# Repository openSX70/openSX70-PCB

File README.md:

# openSX70-PCB
EagleCAD design files for the main PCB of the openSX70 project

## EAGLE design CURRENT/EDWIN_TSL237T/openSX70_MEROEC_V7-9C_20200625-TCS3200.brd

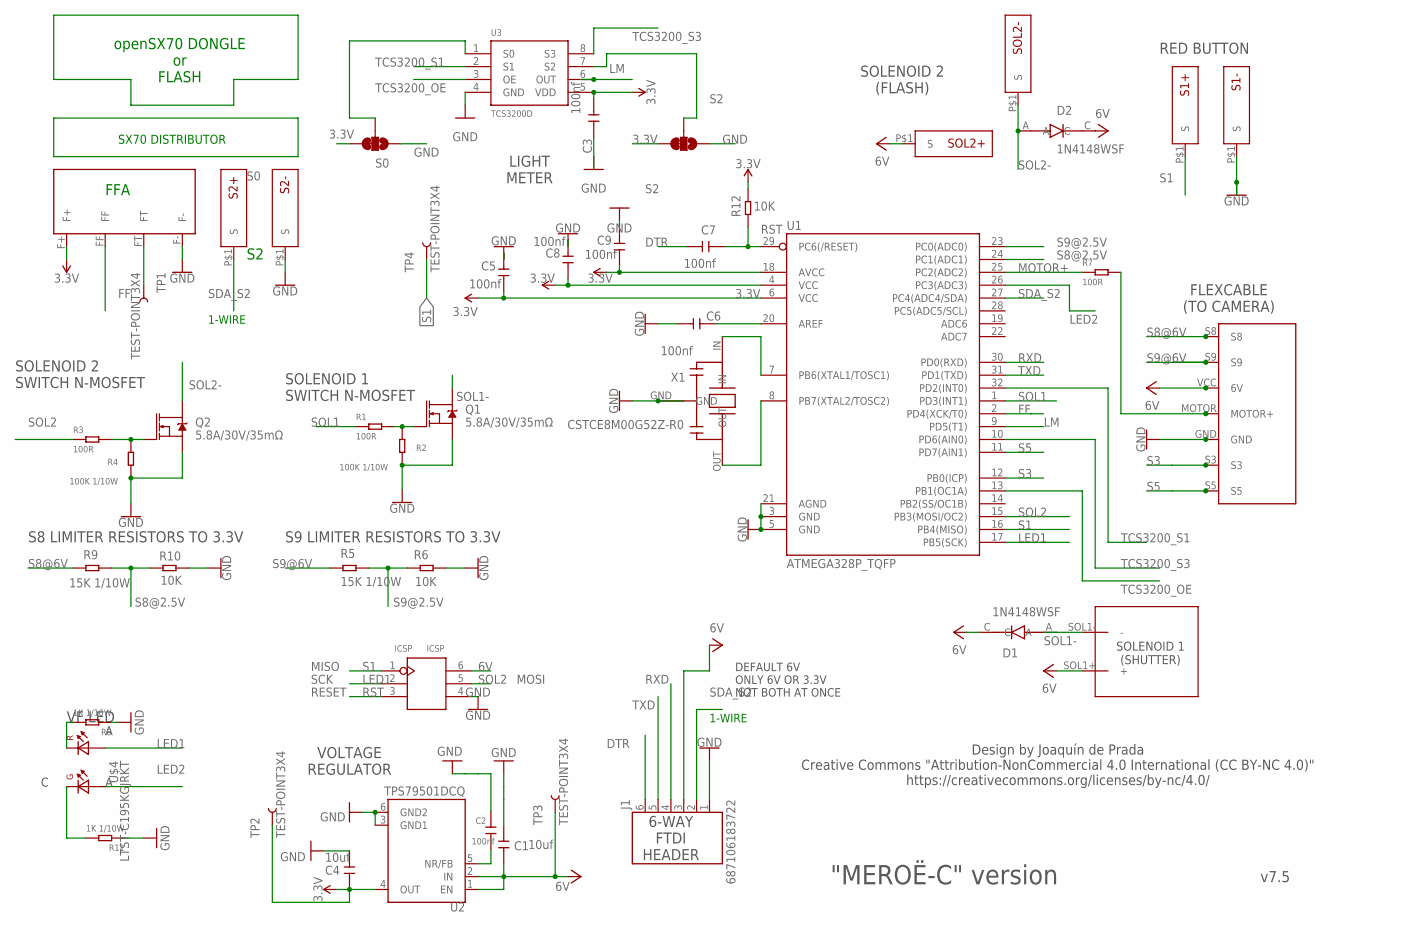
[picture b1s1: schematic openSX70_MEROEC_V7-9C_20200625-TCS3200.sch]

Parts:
C1, C4: 10uf; C0603
C2, C3, C5, C6, C7, C8, C9: 100nf; C0603
D1, D2: 1N4148WSF; SODFL2512X100N
ICSP: ICSP; H2X3-2.54
J1: 687106183722
Q1, Q2: 5.8A/30V/35mΩ; SOT23-3
R1, R3, R7: 100R; R0603
R2, R4: 100K 1/10W; R0603
R5, R9: 15K 1/10W; R0603
R6, R10, R12: 10K; R0603
R8, R11: 1K 1/10W; R0603
S0: S0; SMT-JUMPER_3_1-NC_TRACE_SILK
S1+, S1-, S2+, S2-: SX70-S-PAD-NEW; SX70-S-PAD2
S2: S2; SMT-JUMPER_3_1-NC_TRACE_SILK
SOL1: SX70-SOLENOID1-2PADS; SX70-SOLENOID1-2
SOL2+, SOL2-: SX70-S-PAD-NEW; SX70-S-PAD2
TP1, TP2, TP3, TP4: TEST-POINT3X4; PAD.03X.04
U1: ATMEGA328P_TQFP; TQFP32-08
U2: TPS79501DCQ; SOT127P706X180-6N
U3: TCS3200D; SOIC8
U$1: SX70-7-PAD; SX70-7-PAD-PROPER
U$2: FFA; FFA-PAD-PACKAGE
U$4: LTST-C195KGJRKT; LTST-BILED-15X16
X1: CSTCE8M00G52Z-R0; CFP95P160X100-3N

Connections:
3.3V: C3.1, C4.2, C5.1, C8.1, C9.1, R12.2, S0.3, S2.3, TP2.P$1, U1.4 (VCC), U1.6 (VCC), U1.18 (AVCC), U2.4 (OUT), U3.5 (VDD), U$2.F+
6V: C1.2, D1.C, D2.C, ICSP.6 (VCC), J1.3 (4), SOL1.SOL1+ (+), SOL2+.P$1, TP3.P$1, U2.1 (EN), U2.2 (IN), U$1.VCC (6V)
DTR: C7.1, J1.6 (1)
FF: U1.2 (PD4(XCK/T0)), U$2.FF
GND: C1.1, C2.1, C3.2, C4.1, C5.2, C6.1, C8.2, C9.2, ICSP.4 (GND), J1.1 (6), Q1.2 (S), Q2.2 (S), R2.1, R4.1, R6.2, R8.1, R10.2, R11.1, S0.1, S1-.P$1, S2.1, S2-.P$1, U1.3 (GND), U1.5 (GND), U1.21 (AGND), U2.3 (GND1), U2.6 (GND2), U3.4 (GND), U$1.GND, U$2.F-, X1.GND
LED1: ICSP.2 (SCK), U1.17 (PB5(SCK)), U$4.P$2 (A2)
LED2: U1.26 (PC3(ADC3)), U$4.P$1 (A1)
LM: U1.9 (PD5(T1)), U3.6 (OUT)
MOTOR+: R7.1, U1.25 (PC2(ADC2))
MOTOR-HEADER: R7.2, U$1.MOTOR (MOTOR+)
unnamed: Q1.1 (G), R1.2, R2.2
unnamed: C6.2, U1.20 (AREF)
unnamed: Q2.1 (G), R3.2, R4.2
unnamed: U1.7 (PB6(XTAL1/TOSC1)), X1.IN
unnamed: TP1.P$1, U$2.FT
unnamed: U1.8 (PB7(XTAL2/TOSC2)), X1.OUT
unnamed: S0.2, U3.1 (S0)
unnamed: S2.2, U3.7 (S2)
unnamed: R8.2, U$4.P$4 (K2)
unnamed: C2.2, U2.5 (NR/FB)
unnamed: R11.2, U$4.P$3 (K1)
RST: C7.2, ICSP.3 (RST), R12.1, U1.29 (PC6(/RESET))
RXD: J1.4 (3), U1.30 (PD0(RXD))
S1: ICSP.1 (MISO), S1+.P$1, TP4.P$1, U1.16 (PB4(MISO))
S3: U1.12 (PB0(ICP)), U$1.S3
S5: U1.11 (PD7(AIN1)), U$1.S5
S8@2.5V: R9.2, R10.1, U1.24 (PC1(ADC1))
S8@6V: R9.1, U$1.S8
S9@2.5V: R5.2, R6.1, U1.23 (PC0(ADC0))
S9@6V: R5.1, U$1.S9
SDA_S2: J1.2 (5), S2+.P$1, U1.27 (PC4(ADC4/SDA))
SOL1: R1.1, U1.1 (PD3(INT1))
SOL1-: D1.A, Q1.3 (D), SOL1.SOL1- (-)
SOL2: ICSP.5 (MOSI), R3.1, U1.15 (PB3(MOSI/OC2))
SOL2-: D2.A, Q2.3 (D), SOL2-.P$1
TCS3200_OE: U1.13 (PB1(OC1A)), U3.3 (OE)
TCS3200_S1: U1.32 (PD2(INT0)), U3.2 (S1)
TCS3200_S3: U1.10 (PD6(AIN0)), U3.8 (S3)
TXD: J1.5 (2), U1.31 (PD1(TXD))

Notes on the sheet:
1-WIRE
FFA
LIGHT METER
FLEXCABLE (TO CAMERA)
RED BUTTON
SOLENOID 1 (SHUTTER)
SOLENOID 2 (FLASH)
6-WAY FTDI HEADER
VOLTAGE REGULATOR
S8 LIMITER RESISTORS TO 3.3V
S9 LIMITER RESISTORS TO 3.3V
SOLENOID 2 SWITCH N-MOSFET
SOLENOID 1 SWITCH N-MOSFET
SX70 DISTRIBUTOR
openSX70 DONGLE or FLASH
v7.5
Design by Joaquín de Prada Creative Commons "Attribution-NonCommercial 4.0 International (CC BY-NC 4.0)" https://creativecommons.org/licenses/by-nc/4.0/
"MEROË-C" version
DEFAULT 6V ONLY 6V OR 3.3V NOT BOTH AT ONCE
MISO
SCK
RESET
MOSI
VF LED

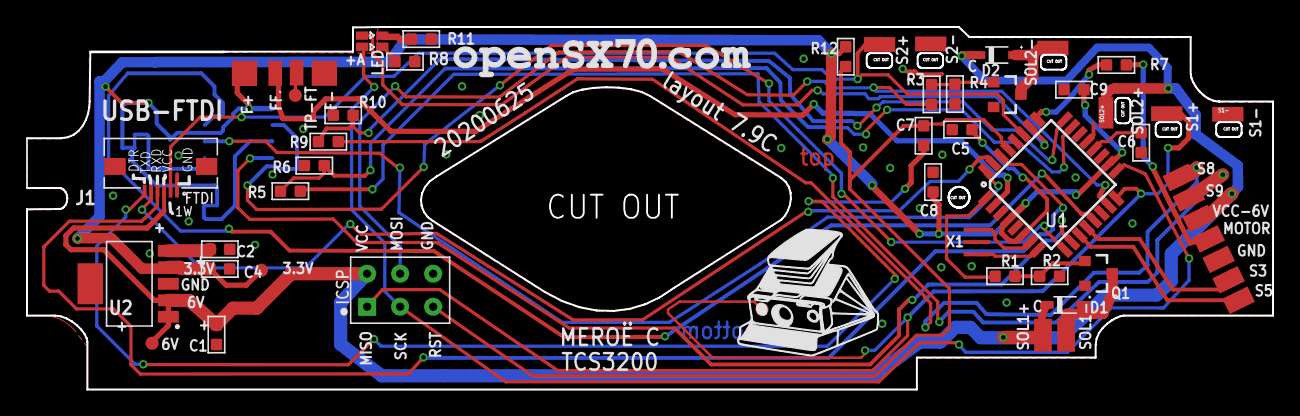
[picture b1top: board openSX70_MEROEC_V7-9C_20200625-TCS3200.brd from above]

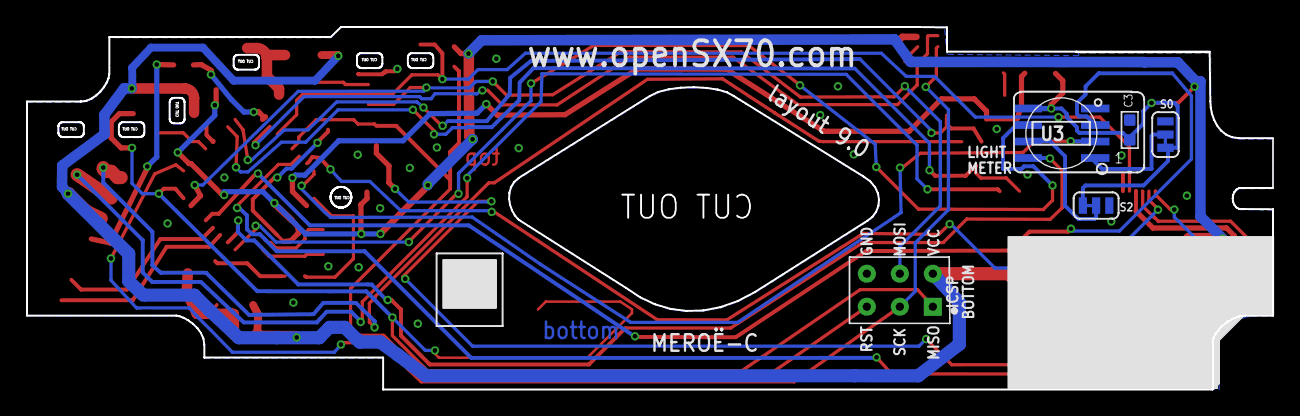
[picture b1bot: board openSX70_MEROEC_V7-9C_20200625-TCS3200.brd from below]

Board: 2 copper layers, 95.9 x 27.9 mm, 47 parts (4 on the bottom side), 39 nets.

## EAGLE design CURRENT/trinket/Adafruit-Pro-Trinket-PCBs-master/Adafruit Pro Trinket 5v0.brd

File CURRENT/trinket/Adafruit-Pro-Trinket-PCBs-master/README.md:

Adafruit-Pro-Trinket-PCBs
=========================

PCB files for Adafruit Pro Trinket 3V & 5V

This is the CAD & PCB data for the Adafruit Trinket
PCB format is EagleCAD schematic and board layout

For more details, check out the product pages at

-----> https://www.adafruit.com/products/2000
and
-----> https://www.adafruit.com/products/2010

Adafruit invests time and resources providing this open source design, 
please support Adafruit and open-source hardware by purchasing 
products from Adafruit!

Designed by Adafruit Industries.  
Creative Commons Attribution, Share-Alike license, check license.txt for more information
All text above must be included in any redistribution

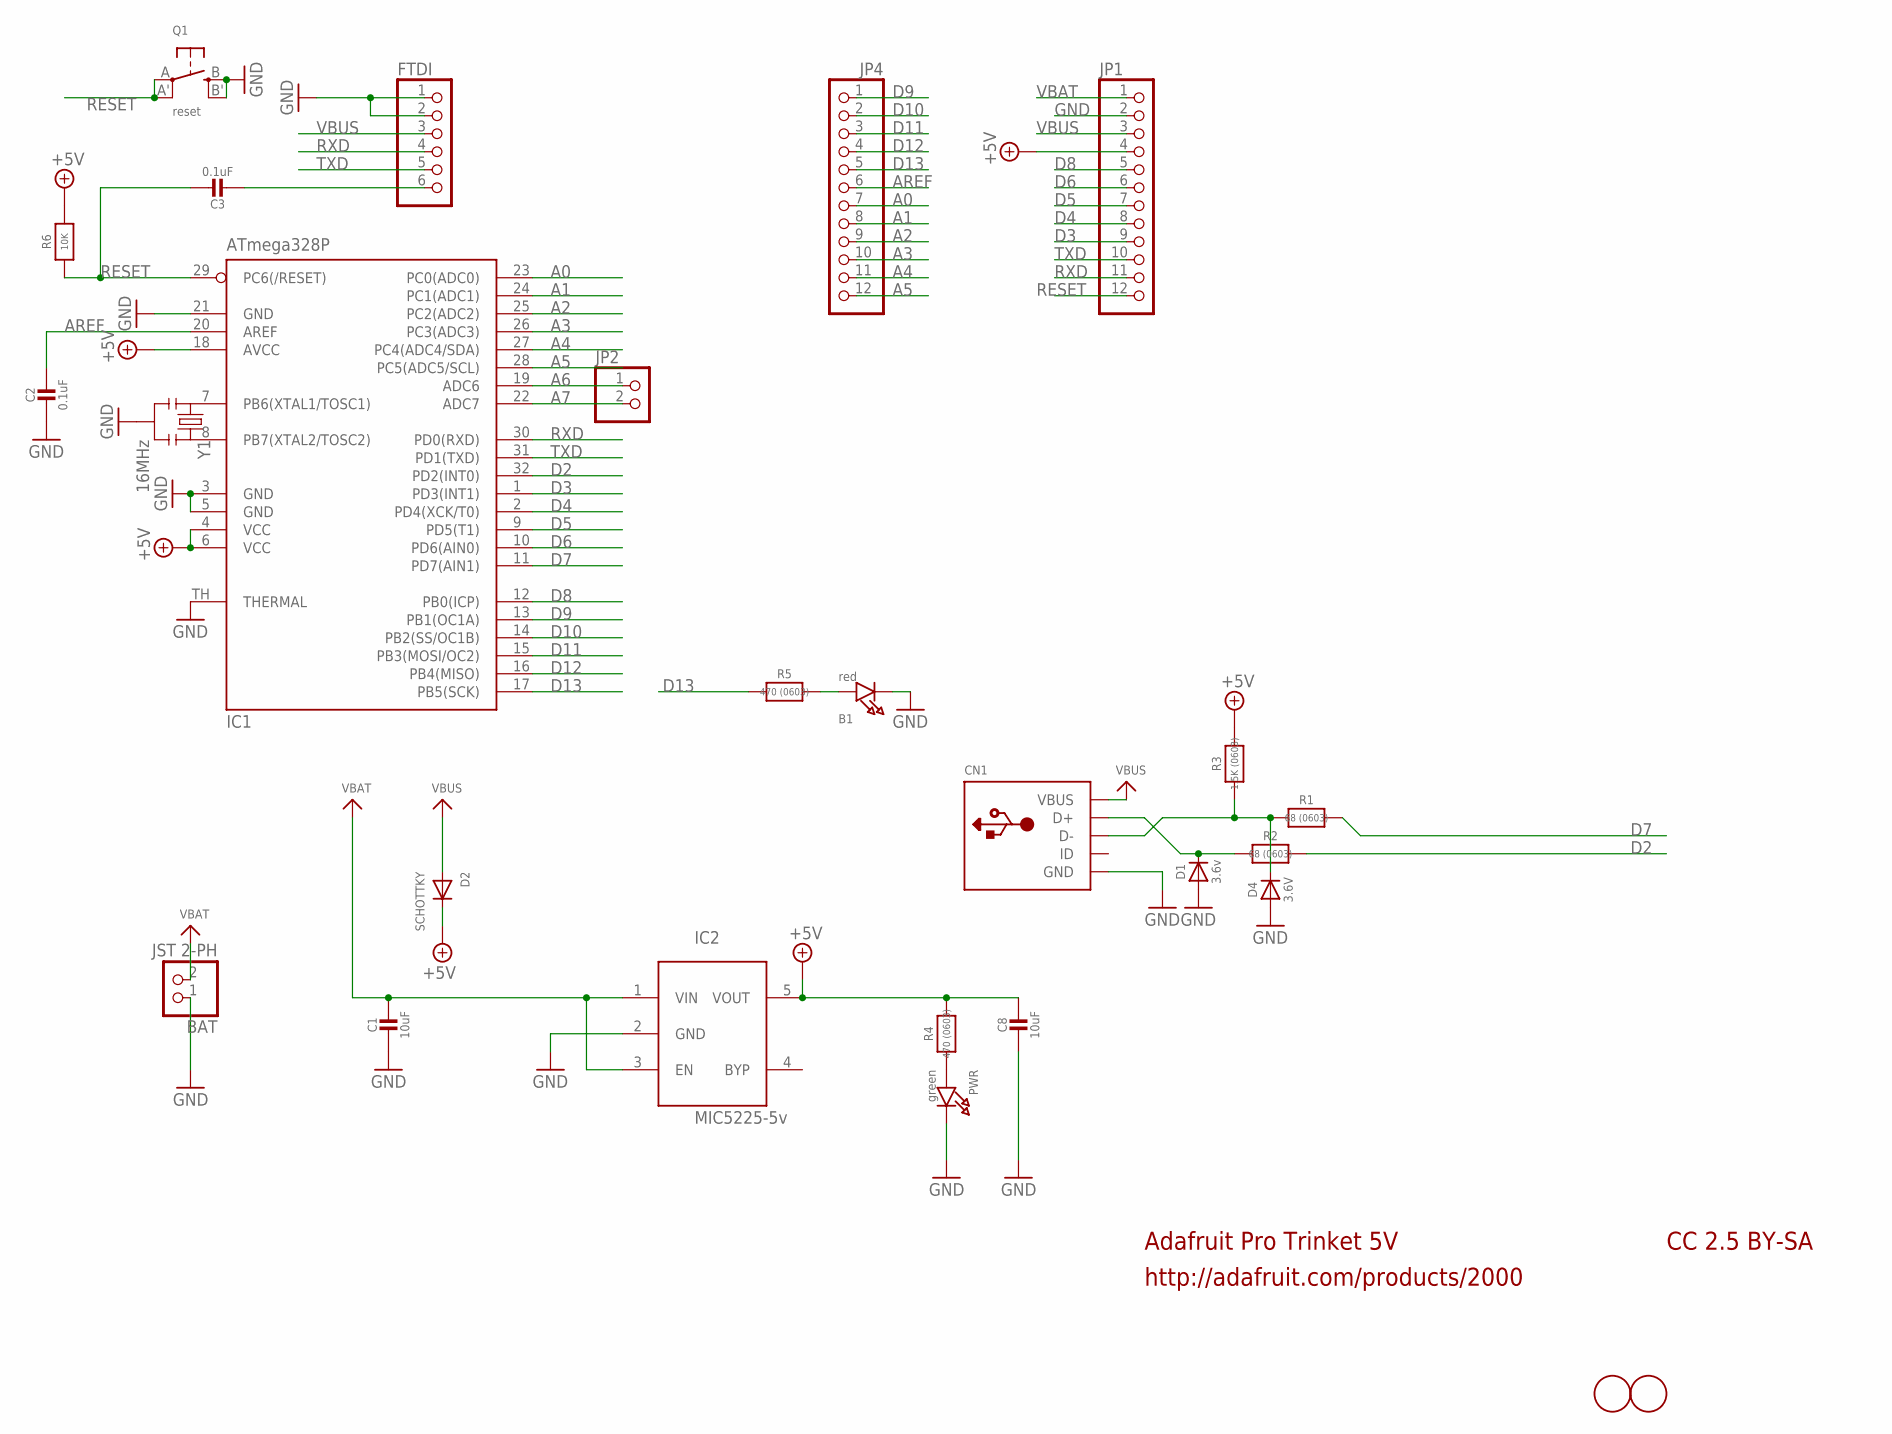
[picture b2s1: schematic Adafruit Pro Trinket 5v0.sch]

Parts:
B1: red; CHIPLED_0805_NOOUTLINE
BAT: JST 2-PH; JSTPH2
C1, C8: 10uF; 0805-NO
C2: 0.1uF; _0805MP
C3: 0.1uF; 0805-NO
CN1: USBMICRO_20329; 4UCONN_20329
D1: 3.6v; SOD-323
D2: SCHOTTKY; SOD-123FL
D4: 3.6V; SOD-323
FTDI: PINHD-1X6CB; 1X06-CLEANBIG
IC1: ATmega328P; MLF32-TH
IC2: MIC5225-5v; SOT23-5L
JP1, JP4: PINHD-1X12-CB; 1X12-CB
JP2: HEADER-1X2ROUND; 1X02_ROUND
PWR: green; CHIPLED_0805_NOOUTLINE
Q1: reset; BTN_KMR2_4.6X2.8
R1, R2: 68 (0603); 0603-NO
R3: 1.5K (0603); 0603-NO
R4, R5: 470 (0603); 0603-NO
R6: 10K; 0805-NO
U$1, U$6: FIDUCIAL; FIDUCIAL_1MM
Y1: 16MHz; RESONATOR-SMD

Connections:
+5V: C8.1, D2.C, IC1.4 (VCC), IC1.6 (VCC), IC1.18 (AVCC), IC2.5 (VOUT), JP1.4, R3.2, R4.2, R6.2
A0: IC1.23 (PC0(ADC0)), JP4.7
A1: IC1.24 (PC1(ADC1)), JP4.8
A2: IC1.25 (PC2(ADC2)), JP4.9
A3: IC1.26 (PC3(ADC3)), JP4.10
A4: IC1.27 (PC4(ADC4/SDA)), JP4.11
A5: IC1.28 (PC5(ADC5/SCL)), JP4.12
A6: IC1.19 (ADC6), JP2.1
A7: IC1.22 (ADC7), JP2.2
AREF: C2.1, IC1.20 (AREF), JP4.6
D2: IC1.32 (PD2(INT0)), R2.2
D3: IC1.1 (PD3(INT1)), JP1.9
D4: IC1.2 (PD4(XCK/T0)), JP1.8
D5: IC1.9 (PD5(T1)), JP1.7
D6: IC1.10 (PD6(AIN0)), JP1.6
D7: IC1.11 (PD7(AIN1)), R1.2
D8: IC1.12 (PB0(ICP)), JP1.5
D9: IC1.13 (PB1(OC1A)), JP4.1
D10: IC1.14 (PB2(SS/OC1B)), JP4.2
D11: IC1.15 (PB3(MOSI/OC2)), JP4.3
D12: IC1.16 (PB4(MISO)), JP4.4
D13: IC1.17 (PB5(SCK)), JP4.5, R5.2
D+: CN1.D+, D1.C, R2.1
D-: CN1.D-, D4.C, R1.1, R3.1
DTR/RTS: C3.2, FTDI.6
GND: B1.C, BAT.1, C1.2, C2.2, C8.2, CN1.BASE@1 (GND), CN1.BASE@2 (GND), CN1.GND, CN1.SPRT@1 (GND), CN1.SPRT@2 (GND), CN1.SPRT@3 (GND), CN1.SPRT@4 (GND), D1.A, D4.A, FTDI.1, FTDI.2, IC1.3 (GND), IC1.5 (GND), IC1.21 (GND), IC1.TH (THERMAL), IC2.2 (GND), JP1.2, PWR.C, Q1.B (S), Q1.B' (S1), Y1.2
unnamed: B1.A, R5.1
unnamed: IC1.8 (PB7(XTAL2/TOSC2)), Y1.3
unnamed: IC1.7 (PB6(XTAL1/TOSC1)), Y1.1
unnamed: PWR.A, R4.1
RESET: C3.1, IC1.29 (PC6(/RESET)), JP1.12, Q1.A, Q1.A' (P1), R6.1
RXD: FTDI.4, IC1.30 (PD0(RXD)), JP1.11
TXD: FTDI.5, IC1.31 (PD1(TXD)), JP1.10
VBAT: BAT.2, C1.1, IC2.1 (VIN), IC2.3 (EN), JP1.1
VBUS: CN1.VBUS, D2.A, FTDI.3, JP1.3

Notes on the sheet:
Adafruit Pro Trinket 5V
http://adafruit.com/products/2000
CC 2.5 BY-SA

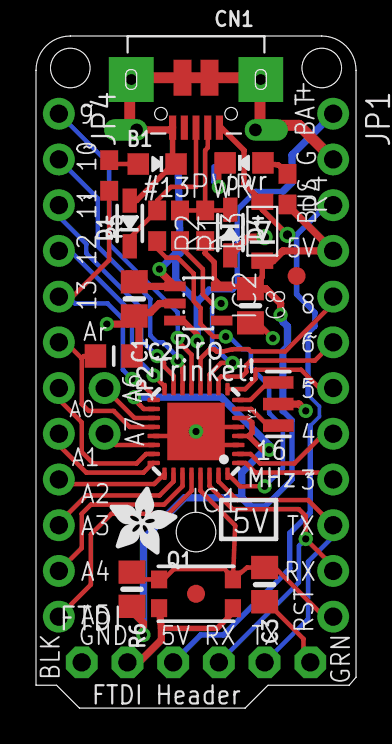
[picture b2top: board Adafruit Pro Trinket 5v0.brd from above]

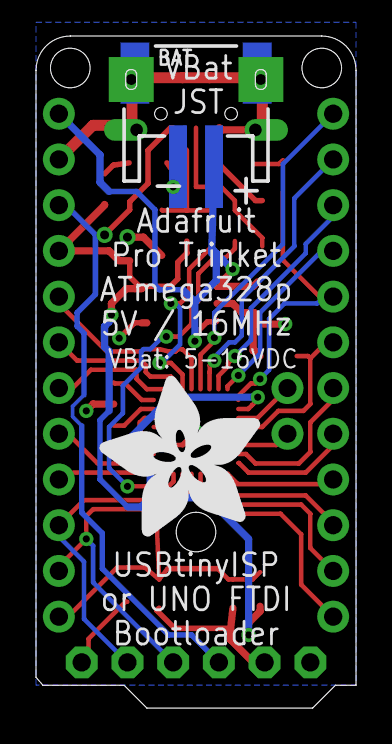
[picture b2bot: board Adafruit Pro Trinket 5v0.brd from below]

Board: 2 copper layers, 17.8 x 37.3 mm, 29 parts (2 on the bottom side), 35 nets.

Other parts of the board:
U$7: ADAFRUIT_3.5MM
U$9: ADAFRUIT_9MM

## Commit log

2017-11-27 set the CC BY-NC 4.0 license for hardware stuff
    You are free to:
    Share — copy and redistribute the material in any medium or format
    Adapt — remix, transform, and build upon the material
    The licensor cannot revoke these freedoms as long as you follow the license terms.
2017-11-27 initial commit of files
    These are the board and the schematic, initial design
2017-11-27 the DXF outline files
    Files you import to create the Dimension layer on Eagle.
2017-11-27 more DXF outline files
    Updated DXF files. Not checked yet
2017-11-27 Eagle schematic and board with connectors
    Eagle schematic and board with connectors. The components are not placed. Good start point to design your own board from scratch.
2017-11-27 Eagle openSX70 pcb layout 2.0
    Layout 2.0
2017-11-27 Eagle main PCB 2.1
    Eagle main PCB 2.1, manufactured by EasyEDA as a test 26/11/2017
2017-11-27 openSX70 main PCB gerbers
    for SEEDSTUDIO FUSION and EasyEDA, check at least .8mm, probably better .6mm or .4mm witdh of the board!
2017-12-16 New "RAW" as a startup for new placement/layout. Changed crystal for one smaller and with caps built in. Created files for new WIP.
2017-12-18 new board work in progress.
2017-12-18 small steps on the board.
2017-12-20 Changed MOTOR pin from 19 to 25. The board is a mess and I have to start over.
2017-12-20 change MOTOR to pin 25 on RAW file.
2017-12-20 new RAW version and WIP version with MOTOR+ to pin 25. RAW version without component layout on board to start from scratch.
2017-12-20 New up-to-date WIP file!
2017-12-21 minor updates in new layout. Routing manually important traces.
2017-12-24 Painfully laying out components and routing, manually.
2017-12-25 Saved a pre-AR version and then different WIP AR.
2017-12-25 Added some vias.
2017-12-29 fixed connections on openSX70 library
2018-01-02 V3.2 added license text. Will do to all brd.
2018-01-02 New version 3.3 changed diode to DZ2J033
2018-01-03 Create new 3.4 "chocolate" version. Looks ok, will do more tests and send it for fabrication. Also created gerbers, remember minimun .8mm, better .6mm or .4mm.
2018-01-03 minor cosmetic changes to "chocolate"
2018-01-03 More cosmetic stuff.
2018-01-03 Added on copper top and bottom for sanity
2018-01-03 I messed versions work/home
2018-01-03 Version 3.4.1 "Chocolate" changed D1 to 1N4148W SOD-123 diode. Created gerbers
2018-01-03 fixed some stuff in the schematic
2018-01-03 Added BOM excel file
2018-01-03 Added correct version number in bottom
2018-01-16 New version 3.5, fixed D1 footprint and some tracks. Added an FTDI 3.3v-6V selection jumper. Change version name to cake
2018-01-16 Lots of small fixes, and fixed cosmetically values, widening track and such.
2018-01-17 New version to fix Solenoid#1 pin error. Minor fix.
2018-01-17 Minor 45º fixes ;-)
2018-01-17 changed sol#1 and FF port to what it should be.
2018-01-17 changed version number and name on schematic
2018-01-17 Changed name on brd and version number.
2018-01-17 Added a protection diode D1 to solenoid#1 for protection. I had assumed that it was built in the solenoid but Phyvine Tong indicated that some later models (alpha) don't have it.
2018-01-17 Added GND 6V and 3.3V test points. Removed a bunch of innecessary vias.
2018-01-17 I keep on tweaking compulsively. Definitely have to stop.
2018-01-18 Added TP to pins 15 16 and 17, for bootloader programming (?)
2018-01-18 Minor fixes, making the board look nicer.
2018-01-18 Minor changes, also added TP SCL and SDA. Created gerbers.
2018-01-18 Cosmetic changes and moved some files (chocolate) to OLD folder.
2018-01-19 Made main 6v track wider from 32mil to 40mil.
2018-01-19 Widening more tracks.
2018-01-19 Latest update
2018-01-19 Outline of the light seal Just lost a bunch of work!!
2018-01-20 Upped to v. 3.7 and changed the date.
2018-01-20 Trying a new component layout, saving the lens seal! NOT ROUTED use Aladdin for now
2018-01-22 Lost track of what I was doing, but basically trying to stay out of the light seal.
2018-01-22 "Saved" Aladdin regarding light-seal issue. Will manufacture. Current 2.8
2018-01-22 final Aladdin v.3.9
2018-01-22 Armonized all VIAS. Minor aesthetic fixes.
2018-01-22 New board design with a FCC or FPC.
2018-01-23 New v.3.9 "Aladdin-fpc" is basically Aladdin with the FTDI header changed to the upper left in the form of a flexible cable.
2018-01-23 Minor changes to Aladdin-fpc 3.9
2018-01-23 Minor changed to v.3.9 FPC with a flat cable .5mm for the FTDI. It is a variant based on the Aladdin v3.8
2018-01-23 Fixing little things in all Aladdin boards
2018-01-24 Minor retouches
2018-01-24 Changes from the office
2018-01-24 Latest and greatest. Go to production????
2018-01-24 Changed MISO/MOSI was all wrong
2018-01-24 This is the newest today.
2018-01-24 trying to figure out Github. From home.
2018-01-25 Changes silkscreen to 2.5V new version 2.9.1
2018-01-26 Manufactured board
2018-02-05 New Aladdin-FPC "C" version
2018-02-06 working on a "manufacturable" board
2018-02-07 Very minor change, making room for programming pad
2018-02-07 Working on an ICSP header
2018-02-08 NEW VERSION 3.9.5S for SeeedStudio Fusion PCBA test
2018-02-09 Removed unnecessary vias, al pads. Minor fixes all over. Getting ready for production!
2018-02-09 new BOM "mix"
2018-02-10 working on a manufacturable version
2018-02-10 Lots of changes in SEEED studio NOW 3.9.6S. Moved a lot of files to OLD folders.
2018-02-11 Working
2018-02-13 New "anniversary" SEEED-only (WIP) PCBA version
2018-02-13 New BOM and new PCB all OPL CPL parts for manufacturing!
2018-02-13 Cleaned the schematic a bit
2018-02-19 changes, octopart BOM
2018-02-19 changed to OPL and CPL footprints
2018-02-19 Seeed components
2018-02-20 Updated to 8.6.3 eagle and more
2018-02-20 Updated office to 8.6.3 minor changes. Rethinking buzzer altogether
2018-02-21 retouches from home. Thinking about a buzzer fix, working on a 10-way FPC both ISCP and FTDI at once
2018-02-21 assembly cues
2018-02-21 Latest with new Buzzer schematic
2018-02-21 Clean-up board and schematic
2018-02-21 Tweaking and tweaking to keep the mind busy.
2018-02-22 And so on...
2018-02-22 New board nickname: Len's&Bellows 5.0 (different from Len's & Bellows 4.x): moved Atmega up, and much more little improvements!
2018-02-23 Major folder rearrangement, latest 5.0 Lens-and-Bellows
2018-02-23 All ready for manufacture!
2018-02-26 New 5.1 version
2018-02-26 Latest versions bypassing Sourcetree
    SourceTree not working from home, tried everything to no avail.
2018-02-26 New "definitive" Len's and Bellows version.
2018-03-27 Current
2018-04-21 Merge branch 'master' of https://github.com/openSX70/openSX70-PCB
    # Conflicts:
    # CURRENT/openSX70_LENS&BELLOWS_V5.2-SEEED_20180226.dxf
2018-05-21 New 5.5 version need a new code-name
2018-05-23 New 5,5 "Pathfinder" with relocated BH1750 and removed buzzer.
2018-06-06 Pathfinder
2018-07-11 updates.
2018-10-05 new layout6 PCB WIP
2018-10-05 Clean up
2018-10-05 NEW NAME FOR LAYOUT 6.0 ALPHA
2018-10-08 working on "ALPHA"
2018-10-08 added quotes to "ALPHA" in the board
2018-10-09 new experimental 6.2: I find no way to fit the FPC connector oposite on the PCB of where it is now, there is just no space.
2018-10-10 ADDED S4A S4B and resistor through jumper J2
2018-10-11 added resistors for different sensor sensibilities
2018-10-15 New layout 6.5 with new flexcable custom connector
2018-10-16 adding to the board
2018-10-24 Work in progress
2018-10-27 acccidentally modified?
2018-10-31 new 7-pad (fixed the component) and WIP on the LED, new LED dual SMD
2018-11-01 new all new layout 7.0
2018-11-02 backtracking to a more safe 6.2.2 version
2018-11-02 working on 6.2.2
2018-11-02 v7 probably abandoned
2018-11-02 6.2.1 WIP
2018-11-03 new board ready for manufacturing 6.2.2
2018-11-04 new layout minor changes
2018-11-04 changed connector S-pad on 6.2.3
2018-11-04 minor fixes or picture graphic
2018-11-04 yet again, new gerbers too
2018-11-05 Simblee eagle files from Sparkfun
2018-11-05 WORKING WITH THE SMALLER ATMEL
2018-11-22 ALPHA BOM (not final)
2018-11-27 new LED outline
2018-11-29 new LED footprint!
2018-12-19 New 6.2.5
2018-12-21 new main PCB fixed 3rd resistor on Photodiode!
2019-02-12 gerbers
2019-03-09 working on new Layout with voltage to frequency AD654 "U2"
2019-03-09 few changes
2019-06-03 organized folders and new PCB for TCS3200 Meröe
2019-06-03 Meröe more or less finished. TCS3200
2019-06-04 NEW RAISED LEDs
2019-06-04 finished Meröe working on TSL235R
2019-06-05 adding decoupling caps
2019-06-05 TSL235 test
2019-06-06 New Meroë 7.5 with 3 added capacitors. Crowded
2019-06-06 completely new layout
2019-06-07 more or less finalised for all 3 chips
2019-11-14 Major cleanup, latest working
2020-04-07 new files and reorganization
2021-01-29 Latest PCBs that I feel confident to push. Contact me if doubts.
2021-02-26 Latest

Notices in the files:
parts and their libraries:
SparkFun-Connectors: Licensing: Creative Commons ShareAlike 4.0 International - https://creativecommons.org/licenses/by-sa/4.0
microbuilder: This work is placed in the public domain, and may be freely used for commercial and non-commercial work with the following conditions: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
